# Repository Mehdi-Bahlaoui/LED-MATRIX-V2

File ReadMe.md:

# LED Matrix v2

## Overview
The LED Matrix v2 project brings together firmware code for controlling an LED matrix and a dedicated Python interface for easier interaction.
This Project is currently divided into two parts:

1. The Code
2. Python Interface

---

## Part 1: The Code

### Description
This section contains the firmware code written for the LED matrix. The code is designed to run on a microcontroller using PlatformIO, managing the LED matrix behaviors, animations, and hardware interactions.

### Project Structure
- **src/**: Contains the main firmware source files.
---

## Part 2: Python Interface

### Description
The Python interface facilitates communication between your computer and the LED matrix device.
It allows testing of LED patterns via a user-friendly script.

---

## License
This project is licensed under the MIT License.

## Contact
For questions or contributions: mehdibahlaoui3@gmail.com

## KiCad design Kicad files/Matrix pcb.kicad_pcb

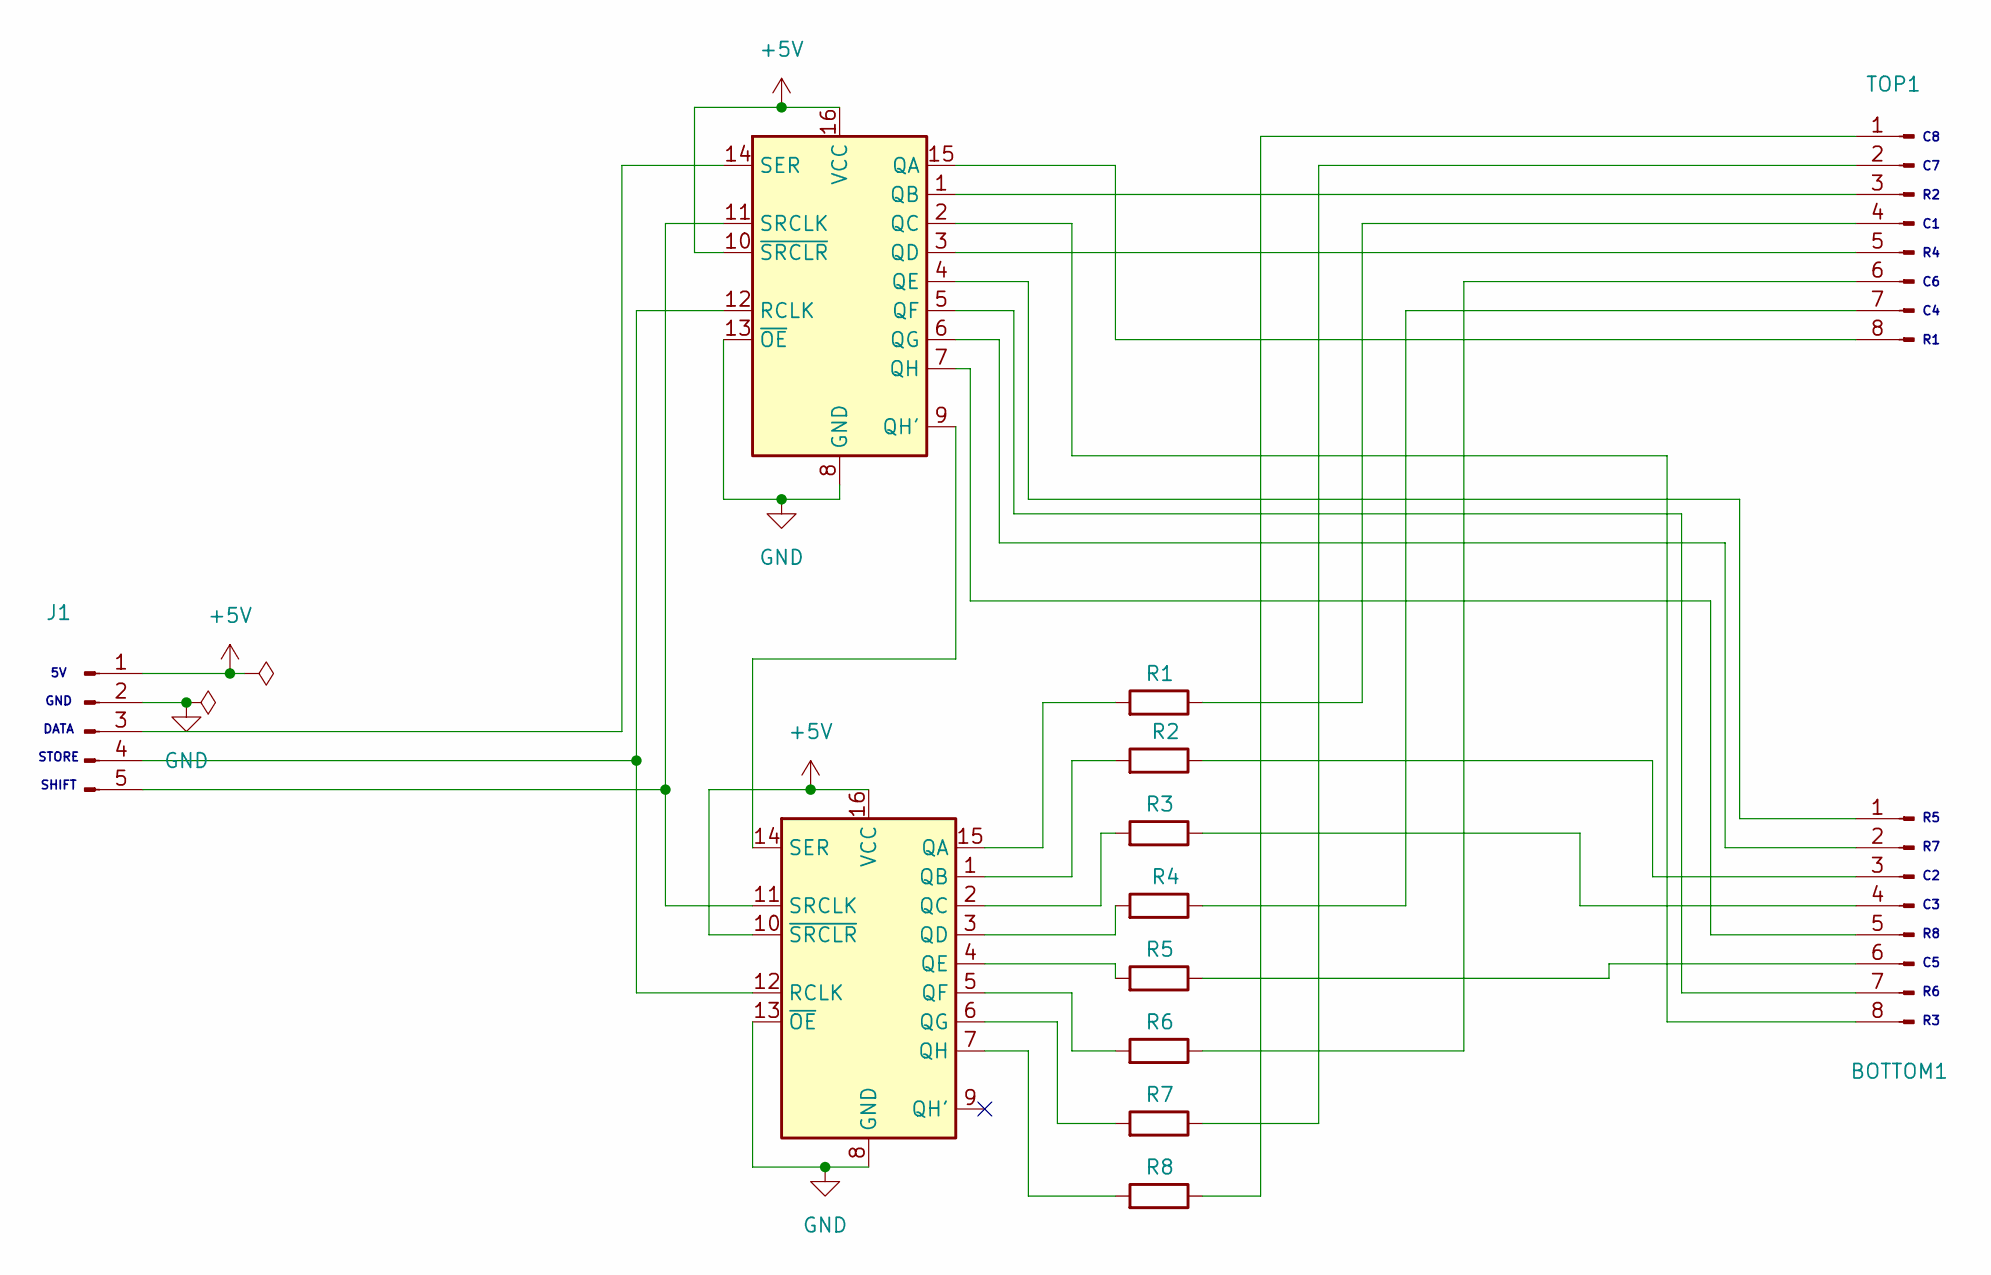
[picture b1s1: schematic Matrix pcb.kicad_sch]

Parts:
BOTTOM1: Conn_01x08_Pin; PinHeader_1x08_P2.54mm_Vertical
Columns1: 74HC595; DIP-16_W7.62mm_LongPads
J1: Conn_01x05_Pin; PinHeader_1x05_P2.54mm_Vertical
R1, R2, R3, R4, R5, R6, R7, R8: R; R_Axial_DIN0207_L6.3mm_D2.5mm_P7.62mm_Horizontal
Rows1: 74HC595; DIP-16_W7.62mm_LongPads
TOP1: Conn_01x08_Pin; PinHeader_1x08_P2.54mm_Vertical

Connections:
+5V: Columns1.10 (~SRCLR), Columns1.16 (VCC), J1.1, Rows1.10 (~SRCLR), Rows1.16 (VCC)
GND: Columns1.8 (GND), Columns1.13 (~OE), J1.2, Rows1.8 (GND), Rows1.13 (~OE)
unnamed: BOTTOM1.1, Rows1.4 (QE)
unnamed: BOTTOM1.2, Rows1.6 (QG)
unnamed: BOTTOM1.3, R2.1
unnamed: BOTTOM1.4, R3.1
unnamed: BOTTOM1.5, Rows1.7 (QH)
unnamed: BOTTOM1.6, R5.1
unnamed: BOTTOM1.7, Rows1.5 (QF)
unnamed: BOTTOM1.8, Rows1.2 (QC)
unnamed: Columns1.15 (QA), R1.2
unnamed: Columns1.1 (QB), R2.2
unnamed: Columns1.2 (QC), R3.2
unnamed: Columns1.3 (QD), R4.2
unnamed: Columns1.4 (QE), R5.2
unnamed: Columns1.5 (QF), R6.2
unnamed: Columns1.6 (QG), R7.2
unnamed: Columns1.7 (QH), R8.2
unnamed: Columns1.12 (RCLK), J1.4, Rows1.12 (RCLK)
unnamed: Columns1.14 (SER), Rows1.9 (QH')
unnamed: Columns1.11 (SRCLK), J1.5, Rows1.11 (SRCLK)
unnamed: J1.3, Rows1.14 (SER)
unnamed: Rows1.15 (QA), TOP1.8
unnamed: Rows1.1 (QB), TOP1.3
unnamed: Rows1.3 (QD), TOP1.5
unnamed: R8.1, TOP1.1
unnamed: R7.1, TOP1.2
unnamed: R1.1, TOP1.4
unnamed: R6.1, TOP1.6
unnamed: R4.1, TOP1.7

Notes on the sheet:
5V GND DATA STORE SHIFT
C8 C7 R2 C1 R4 C6 C4 R1
R5 R7 C2 C3 R8 C5 R6 R3

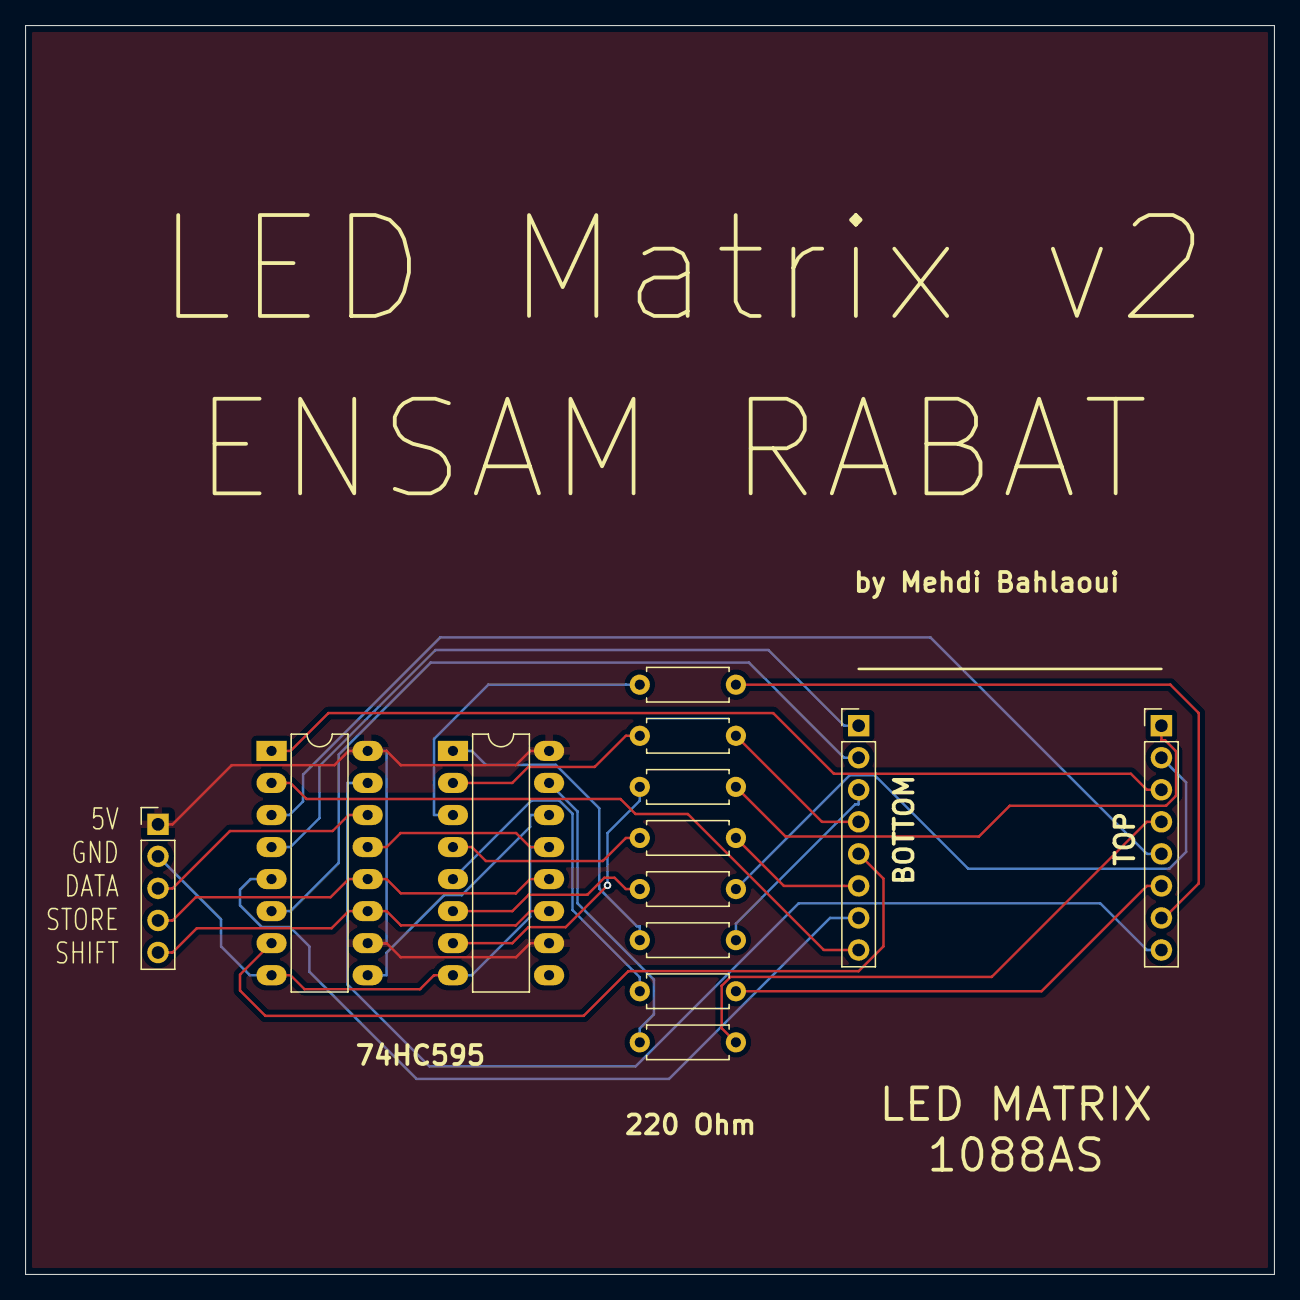
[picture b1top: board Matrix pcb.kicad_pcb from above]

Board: 2 copper layers, 99.0 x 99.0 mm, 13 parts (0 on the bottom side), 30 nets.

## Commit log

2025-02-01 first commit lahomayassiir
2025-02-02 added animation cpp file
2025-02-07 just added readMe , assets and corrected code a bit
2025-02-17 just quality of life improuvements
2025-02-19 add 60% of tetris logic
2025-02-20 tetris done -big win
2025-02-23 improved ReadMe
2025-02-23 modified image in ReadMe
2025-02-27 Update .gitignore to ignore new files and directories
2025-02-27 Added Kicad and gerber files for Matrix PCB
2025-04-20 snake first code
2025-04-20 input handling via serial monitor
2025-05-07 snake game working with wasd keys
